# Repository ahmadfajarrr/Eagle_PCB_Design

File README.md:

# Eagle_PCB_Design
This is a repository all Eagle PCB Design

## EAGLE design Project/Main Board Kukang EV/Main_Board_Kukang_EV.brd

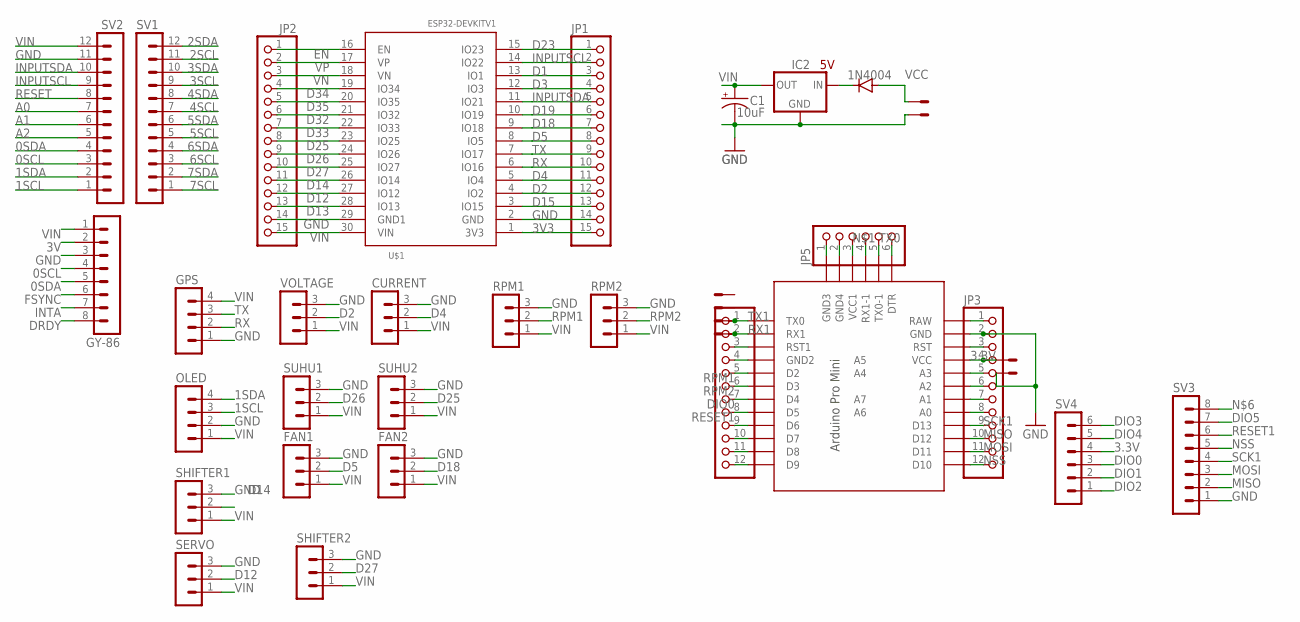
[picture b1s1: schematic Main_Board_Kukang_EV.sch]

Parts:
C1: 10uF; E5-10,5
CURRENT: MA03-1
D1: 1N4004; DO41-10
ESC_BOARD: 22-23-2021
FAN1, FAN2: MA03-1
GPS: MA04-1
GY-86: MA08-1
IC2: V_REG_78XX; V78W_BACKWARDS
JP1, JP2: PINHD-1X15; 1X15
JP3, JP4: PINHD-1X12; 1X12
JP5: PINHD-1X6; 1X06
OLED: MA04-1
POWET: 22-23-2021
RPM1, RPM2: MA03-1
SERVO: MA03-1
SHIFTER1, SHIFTER2: MA03-1
SUHU1, SUHU2: MA03-1
SV1, SV2: MA12-1
SV3: MA08-1
SV4: MA06-1
U$1: ESP32DEVKITV1; ESP32-DEVKITV1
U$2: PRO-MINI-2
UART_MAIN_BOARD: 22-23-2021
VBAT: 22-23-2021
VOLTAGE: MA03-1

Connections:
0SCL: GY-86.4, SV2.3
0SDA: GY-86.5, SV2.4
1SCL: OLED.3, SV2.1
1SDA: OLED.4, SV2.2
2SCL: SV1.11
2SDA: SV1.12
3.3V: JP3.4, POWET.1, SV4.4, U$2.VCC
3SCL: SV1.9
3SDA: SV1.10
3V: GY-86.2
3V3: JP1.15, U$1.1 (3V3)
4SCL: SV1.7
4SDA: SV1.8
5SCL: SV1.5
5SDA: SV1.6
6SCL: SV1.3
6SDA: SV1.4
7SCL: SV1.1
7SDA: SV1.2
A0: SV2.7
A1: SV2.6
A2: SV2.5
D1: JP1.3, U$1.13 (IO1)
D2: JP1.12, U$1.4 (IO2), VOLTAGE.2
D3: JP1.4, U$1.12 (IO3)
D4: CURRENT.2, JP1.11, U$1.5 (IO4)
D5: FAN1.2, JP1.8, U$1.8 (IO5)
D12: JP2.12, SERVO.2, U$1.27 (IO12)
D13: JP2.13, U$1.28 (IO13)
D14: JP2.11, SHIFTER1.2, U$1.26 (IO14)
D15: JP1.13, U$1.3 (IO15)
D18: FAN2.2, JP1.7, U$1.9 (IO18)
D19: JP1.6, U$1.10 (IO19)
D23: JP1.1, U$1.15 (IO23)
D25: JP2.8, SUHU2.2, U$1.23 (IO25)
D26: JP2.9, SUHU1.2, U$1.24 (IO26)
D27: JP2.10, SHIFTER2.2, U$1.25 (IO27)
D32: JP2.6, U$1.21 (IO32)
D33: JP2.7, U$1.22 (IO33)
D34: JP2.4, U$1.19 (IO34)
D35: JP2.5, U$1.20 (IO35)
DIO0: JP4.7, SV4.3, U$2.D4
DIO1: JP4.9, SV4.2, U$2.D6
DIO2: SV4.1
DIO3: SV4.6
DIO4: SV4.5
DIO5: SV3.7
DRDY: GY-86.8
EN: JP2.1, U$1.16 (EN)
FSYNC: GY-86.6
GND: C1.-, CURRENT.3, FAN1.3, FAN2.3, GPS.1, GY-86.3, IC2.GND, JP1.14, JP2.14, JP3.2, OLED.2, POWET.2, RPM1.3, RPM2.3, SERVO.3, SHIFTER1.3, SHIFTER2.3, SUHU1.3, SUHU2.3, SV2.11, SV3.1, U$1.2 (GND), U$1.29 (GND1), U$2.GND, VBAT.2, VOLTAGE.3
INPUTSCL: JP1.2, SV2.9, U$1.14 (IO22)
INPUTSDA: JP1.5, SV2.10, U$1.11 (IO21)
INTA: GY-86.7
MISO: JP3.10, SV3.2, U$2.D12
MOSI: JP3.11, SV3.3, U$2.D11
unnamed: JP5.3, U$2.VCC1
unnamed: JP3.8, U$2.A0
unnamed: JP3.7, U$2.A1
unnamed: D1.C, IC2.IN
unnamed: JP3.6, U$2.A2
unnamed: JP3.5, U$2.A3
unnamed: JP3.3, U$2.RST
unnamed: JP3.1, U$2.RAW
unnamed: JP4.3, U$2.RST1
unnamed: JP4.4, U$2.GND1 (GND2)
unnamed: JP4.10, U$2.D7
unnamed: JP4.11, U$2.D8
unnamed: JP4.12, U$2.D9
unnamed: JP5.6, U$2.DTR
unnamed: JP5.2, U$2.GND3 (GND4)
unnamed: JP5.1, U$2.GND2 (GND3)
NSS: JP3.12, SV3.5, U$2.D10
RESET: SV2.8
RESET1: JP4.8, SV3.6, U$2.D5
RPM1: JP4.5, RPM1.2, U$2.D2
RPM2: JP4.6, RPM2.2, U$2.D3
RX: GPS.2, JP1.10, U$1.6 (IO16)
RX0: JP5.4, U$2.RX1-1
RX1: JP4.2, U$2.RX1, UART_MAIN_BOARD.2
SCK1: JP3.9, SV3.4, U$2.D13
TX: GPS.3, JP1.9, U$1.7 (IO17)
TX0: JP5.5, U$2.TX0-1
TX1: JP4.1, U$2.TX0, UART_MAIN_BOARD.1
VCC: D1.A, VBAT.1
VIN: C1.+, CURRENT.1, FAN1.1, FAN2.1, GPS.4, GY-86.1, IC2.OUT, JP2.15, OLED.1, RPM1.1, RPM2.1, SERVO.1, SHIFTER1.1, SHIFTER2.1, SUHU1.1, SUHU2.1, SV2.12, U$1.30 (VIN), VOLTAGE.1
VN: JP2.3, U$1.18 (VN)
VP: JP2.2, U$1.17 (VP)

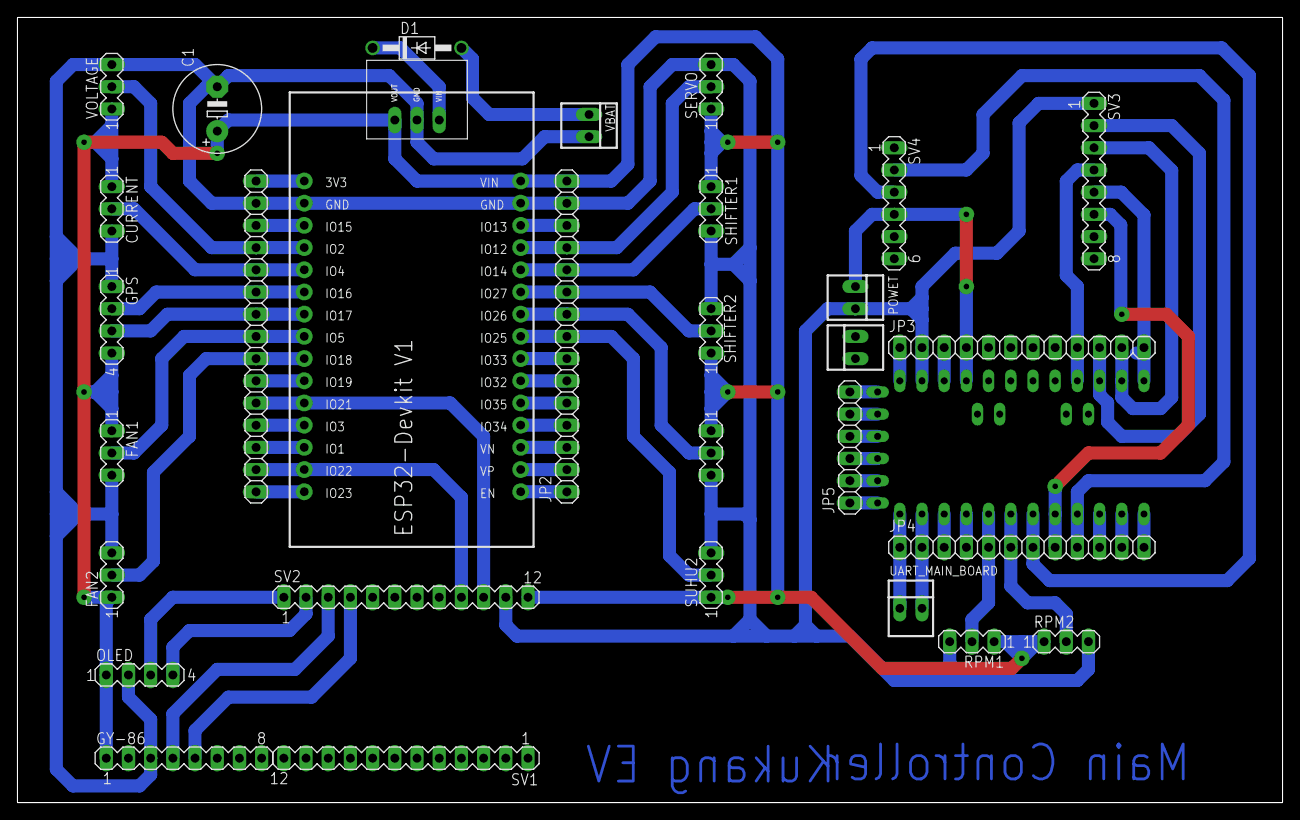
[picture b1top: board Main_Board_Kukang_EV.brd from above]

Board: 2 copper layers, 144.8 x 89.8 mm, 32 parts (0 on the bottom side), 64 nets.

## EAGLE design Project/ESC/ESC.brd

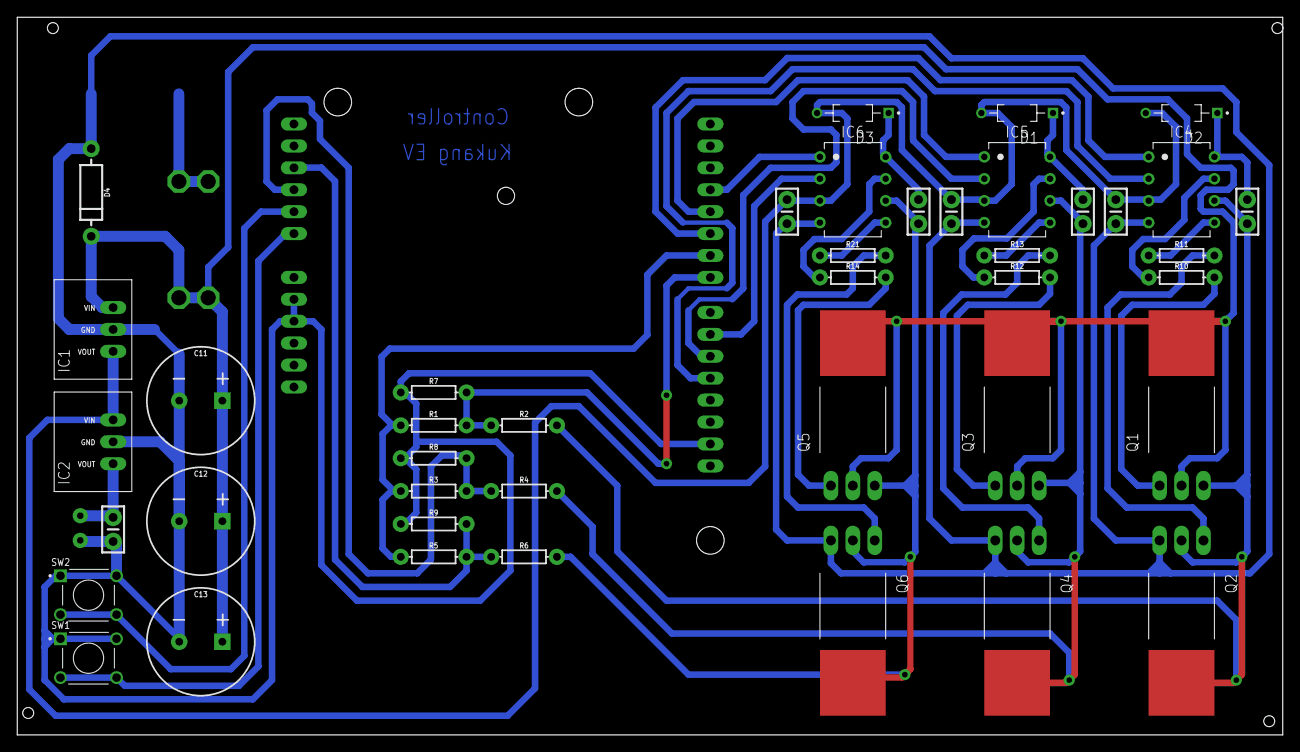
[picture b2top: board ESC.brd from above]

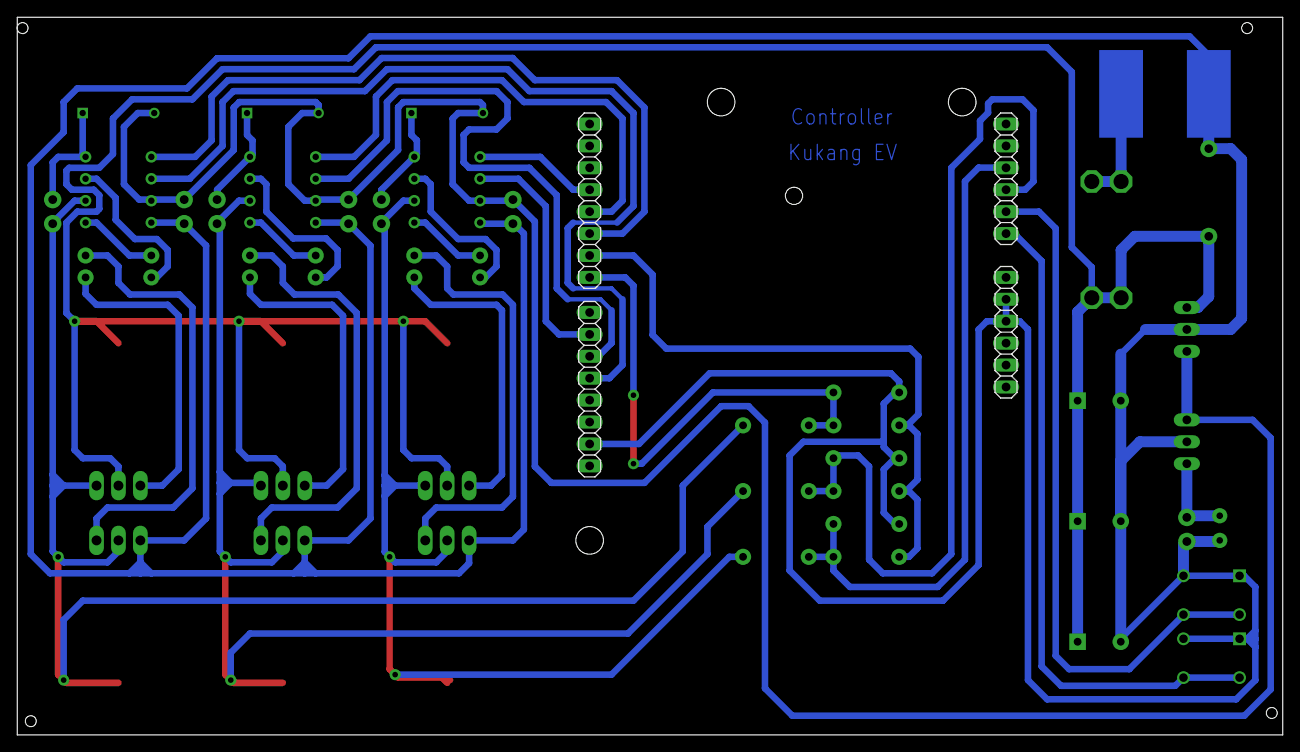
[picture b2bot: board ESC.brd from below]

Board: 2 copper layers, 146.7 x 83.2 mm, 46 parts (3 on the bottom side), 35 nets.

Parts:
C4: 1uF; CAP-PTH-SMALL-KIT
C5, C7, C9: 10uF; CAP-PTH-SMALL-KIT
C6, C8, C10: 2.2uF; CAP-PTH-SMALL-KIT
C11, C12, C13: 470uF; CPOL-RADIAL-5MM-10MM
D1, D2, D3: 1N4148; DIOAD829W49L456D191
D4: TVS; DIODE-1N4001
IC1, IC2: V78W_BACKWARDS
IC3: ARDUINO2009
IC4, IC5, IC6: L6387EDIP8; DIP762W53P254L1092H508Q8B
J2: FUSE; AUTO_FUSE
Q1, Q2, Q3, Q4, Q5, Q6: TO-220-FLAT
R1, R2, R3, R4, R5, R6: 33k; AXIAL-0.3
R7, R8, R9: 10k; AXIAL-0.3
R10, R11, R12, R13, R14, R21: 10; AXIAL-0.3
SW1, SW2: 1825910-6; SW_1825910-6-4
U$9, U$10: PAD

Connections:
5V: C4.1, IC2.OUT
BEMF_A: IC3.20, R1.P$2, R2.P$1, R7.P$2
BEMF_B: IC3.9, R3.P$2, R4.P$1, R8.P$2
BEMF_C: IC3.10, R5.P$2, R6.P$1, R9.P$2
COM_A: C6.2, IC4.6, Q1.3, Q2.2, Q2.PAD, R2.P$2
COM_B: C8.2, IC5.6, Q3.3, Q4.2, Q4.PAD, R4.P$2
COM_C: C10.2, IC6.6, Q5.3, Q6.2, Q6.PAD, R6.P$2
CTRL_AH: IC3.24, IC4.2
CTRL_AL: IC3.18, IC4.1
CTRL_BH: IC3.23, IC5.2
CTRL_BL: IC3.17, IC5.1
CTRL_CH: IC3.22, IC6.2
CTRL_CL: IC3.16, IC6.1
DRV_AH: IC4.7, R10.P$1
DRV_AL: IC4.5, R11.P$1
DRV_BH: IC5.7, R12.P$1
DRV_BL: IC5.5, R13.P$1
DRV_CH: IC6.7, R14.P$1
DRV_CL: IC6.5, R21.P$1
GND: C4.2, C5.2, C7.2, C9.2, C11.-, C12.-, C13.-, D4.A, IC1.GND, IC2.GND, IC3.4, IC3.5, IC3.27, IC4.4, IC5.4, IC6.4, Q2.3, Q4.3, Q6.3, R7.P$1, R8.P$1, R9.P$1, SW1.1, SW1.2, SW2.1, SW2.2, U$10.PAD
unnamed: C8.1, D1.C, IC5.8
unnamed: C10.1, D3.C, IC6.8
unnamed: Q1.1, R10.P$2
unnamed: Q3.1, R12.P$2
unnamed: C6.1, D2.C, IC4.8
unnamed: IC3.7, SW1.3, SW1.4
unnamed: IC3.8, SW2.3, SW2.4
unnamed: Q4.1, R13.P$2
unnamed: Q5.1, R14.P$2
unnamed: Q6.1, R21.P$2
unnamed: Q2.1, R11.P$2
VDD: C5.1, C7.1, C9.1, D1.A, D2.A, D3.A, IC1.OUT, IC2.IN, IC4.3, IC5.3, IC6.3
V_BEMF: IC3.19, R1.P$1, R3.P$1, R5.P$1
V_PREFUSE1: J2.1A, J2.1B, U$9.PAD
V_RAW: C11.+, C12.+, C13.+, D4.C, IC1.IN, J2.2A, J2.2B, Q1.2, Q1.PAD, Q3.2, Q3.PAD, Q5.2, Q5.PAD

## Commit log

2023-07-25 first upload

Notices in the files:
parts and their libraries:
SparkFun-Capacitors: Licensing: Creative Commons ShareAlike 4.0 International - https://creativecommons.org/licenses/by-sa/4.0
